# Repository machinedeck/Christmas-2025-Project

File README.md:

# Christmas 2025 Project

## Background

In the Philippines :philippines:, Christmas is usually the most awaited and favorite season of all time. Starting from September, the ambience transitions into a much jollier and brighter side with occassional Mariah Carey's hit _All I Want for Christmas Is You_ playing on the street. This light and invigorating spirit is what sets Filipino culture apart after having been in Europe for two years. Now, being able to return home with all the brand new and more reinforced knowledge I gathered from my master's studies, I encouraged my creativity to embark on a project that utilized the available electronics materials I had at hand. I intentionally finished this project right before Christmas time so I could run  it while we listened to Christmas songs on TV&ndash;which was a really exciting way to celebrate this season!

To start off, this project consisted of two parts: the _**screen**_ and the _**lights**_. Each part has its own microcontroller unit (MCU)&ndash;the **_ATmega328p_**&ndash;mounted on an Arduino UNO board. 

The 8x8 matrix tube **screen** flashes the `MERRY XMAS!` message moving from right to left. On the other hand, the **lights** part consists of four LEDS (red, green, yellow and blue), which have five different lighting configurations with the last one being the combination of the first four in a consecutive manner. More details about them are explained in the later sections.

## Materials
These are the materials I used for each part:

**Screen**
- **1088BS** 8x8 matrix tube screen (Documentation can be found in this [link](https://www.topliteusa.com/uploadfile/2014/0825/A-1088BS.pdf). Similar matrix can be used but _always refer to its datasheet_ because I did not use any driver to run it, and the pins have to be connected accordingly to flash what you intend to show.)
- Eight **1k&ohm;-resistors**
- One **tactile switch**
- **Arduino UNO** development board with **ATmega328p** microncontroller
- Wires
- _Optional:_ One **9V battery**

**Lights**
- Four **LEDs** (can be any color, but I used red, green, yellow and blue)
- Four **1k&ohm;-resistors**
- One **tactile switch**
- **Arduino UNO** development board with **ATmega328p** microncontroller
- Wires
- _Optional:_ One **9V battery**

## Schematic

### Screen

<p align = "center"><b>Figure 1.</b> Schematic diagram of the wire connections of the 1088BS matrix to the Arduino UNO development board controlled by a switch in pull-up setting. I did not find any matrix design in Tinkercad so I just put its detailed schematics as an array of LEDs. This design was created from this website: <a href = "https://www.circuit-diagram.org/editor/">https://www.circuit-diagram.org/editor/</a>.</p>

The general circuit design for the **screen** part is provided above. The matrix represented as an array of LEDs has also been documented as such in its datasheet [here](https://www.topliteusa.com/uploadfile/2014/0825/A-1088BS.pdf). It is important to note that the matrix does not have its own internal resistors as given in **Figure 1**. This is the reason that there are eight 1k&ohm;-resistors included in the materials. There is a switch included which turns the screen _ON_ and _OFF_. However, this is just the circuit connections, and its working function is defined by the Arduino code uploaded to the microcontroller.

### Lights

<p align = "center"><b>Figure 2.</b> Breadboard connections for the four-LED system controlled by a switch in pull-up configuration. Schematics created from <a href = "https://www.tinkercad.com/">https://www.tinkercad.com/</a> using the circuits option.</p>

For this part, there are LED light array configuration as follows, controlled by pressin a button in a chronological order:
- **Case 1:** Lights fade in then fade out
- **Case 2:** Lights blink
- **Case 3:** Light "pulse" going from one LED to the next. Goes to the first LED after it reaches the last LED.
- **Case 4:** Two sets of LEDs alternate blinking
- **Case 5:** Cases 1-4

Once all the cases have been performed, the LEDs just turn off. Pressing the button reinitiates the cases.

## Codes
Before uploading the codes into the microcontrollers, make sure to install the **Arduino IDE**. Set the board to `Arduino UNO` (can be downloaded [here](https://www.arduino.cc/en/software/)) and make sure that there is a port connection. Once initialized, the following codes must be uploaded to two separate Arduino development boards:
- **Screen:** [`screen.ino`](https://github.com/machinedeck/Christmas-2025-Project/blob/main/screen/screen.ino)
- **Lights:** [`lights.ino`](https://github.com/machinedeck/Christmas-2025-Project/blob/main/lights/lights.ino)

For [`screen.ino`](https://github.com/machinedeck/Christmas-2025-Project/blob/main/screen/screen.ino), I had to manually design the array for the `MERRY XMAS!` message in Excel, then convert them into a `.CSV` file to copy the array into Arduino code. All these information can be found in the following files: `screen_data.txt`, `screen_data.csv`, and `screen_data.xlsx`. Moreover, upon researching, it could be impossible to, say, individually control an array element of the matrix at a time. This is where I struggled the most because I initialized the matrix to a some array of 0's and 1's, but I ended up having one column all turned _ON_ when only a few has to be such. For this, **I had to resort to ChatGPT to seek help**. **I am highlighting this point to go back and understand this matter later on**, I just needed to finish it before Christmas.

For [`lights.ino`](https://github.com/machinedeck/Christmas-2025-Project/blob/main/lights/lights.ino), I was mostly inspired by the lighting mechanism of the Christmas lights displayed outside my neighbor's house. That's where I got the idea of changing configurations, but allows the user to change it at will with a switch.

For both codes, I used switches to control their initialization, termination and configurations by utilizing the [`attachInterrupt()`](https://docs.arduino.cc/language-reference/en/functions/external-interrupts/attachInterrupt/). This interrupt function is initialized in the setup.

## Comments
I noticed that for the **lights** part, I noticed some misalignments with the button press and the LED light configuration. I have not quantified this disparity nor possible delay but there could be some synchronization error, or the with the code itself. I noticed this especially in **Case 5**, where it is supposed to start from **Case 1**. However, there were instances where it just turned _OFF_ or does not start with **Case 1**. I suspect that it might have to do with the code because I once ran the script printing a defined "counter" value, and there was a little problem.

Furthermore, I experienced some memory problem during the course of code development. Before this, I was not able to control the lights independently, which I resolved by using the [`millis()`](https://docs.arduino.cc/language-reference/en/functions/time/millis/) function to avoid blocking code with [`delay()`](https://docs.arduino.cc/language-reference/en/functions/time/delay/). Now, with memory, I have realized how efficient programming is important to expedite process and save storage. For this reason I launched this [repository](https://github.com/machinedeck/Firmware-Programming-1) to learn about efficient embedded programming using registers in C++.

## KiCAD
I also tried to make a KiCAD design, which is provided in this [folder](https://github.com/machinedeck/Christmas-2025-Project/tree/main/xmas).

## Disclaimer
I used ChatGPT mainly to debug my codes and/or seek help regarding their functionalities.

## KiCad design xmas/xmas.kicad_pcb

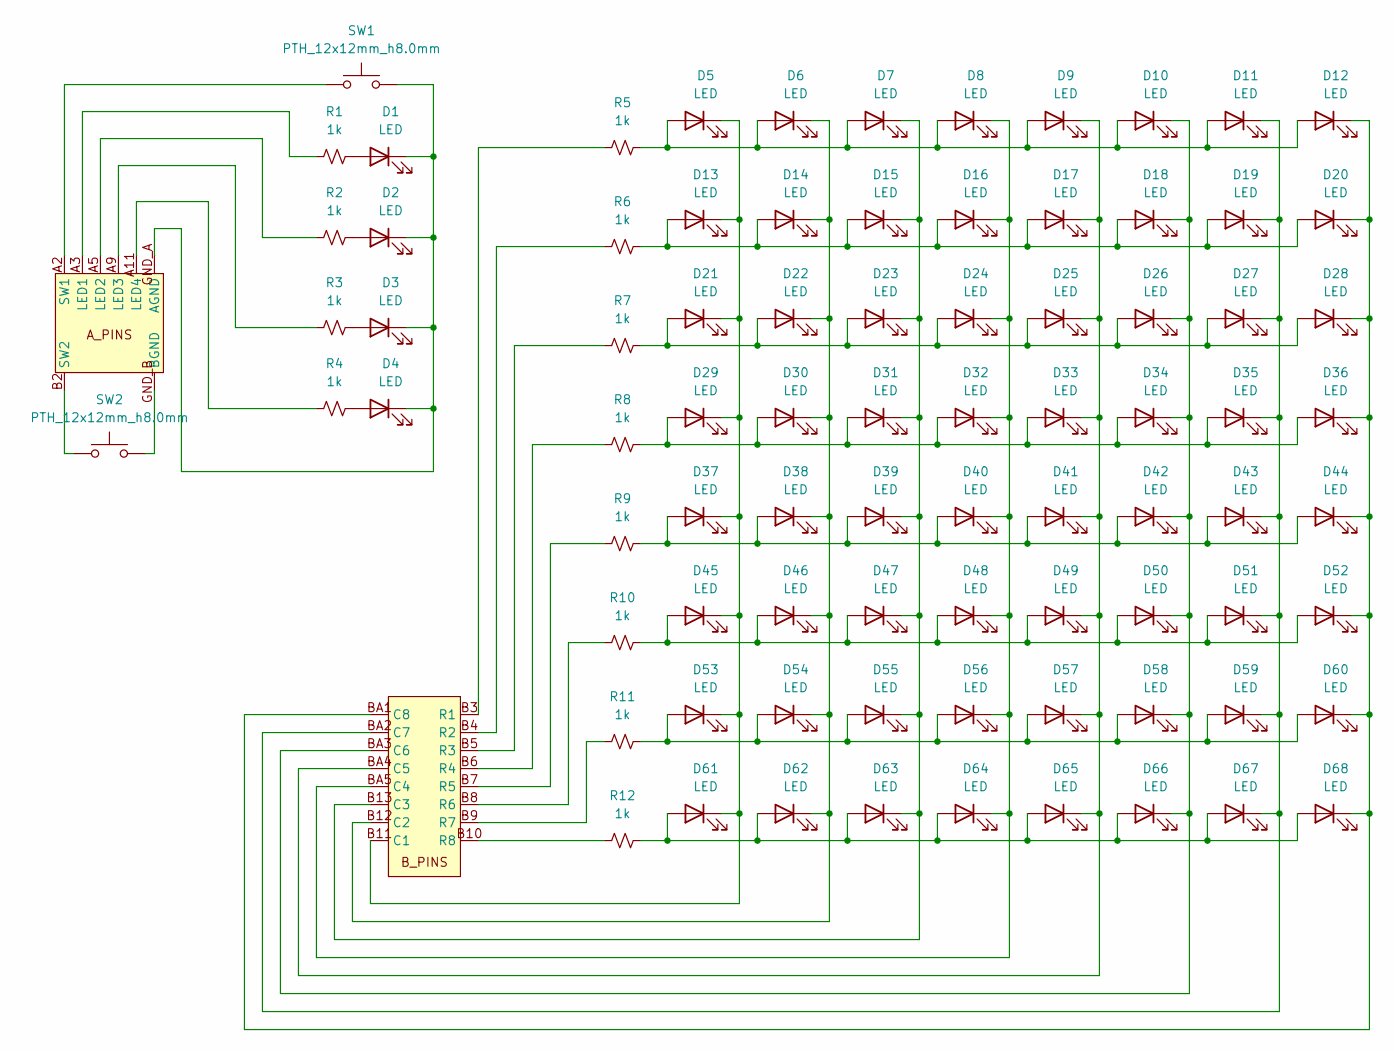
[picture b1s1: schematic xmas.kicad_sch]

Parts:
D1, D2, D3, D4: LED; LED_D3.0mm
D5, D6, D7, D8, D9, D10, D11, D12, D13, D14, D15, D16, D17, D18, D19, D20, D21, D22, D23, D24, D25, D26, D27, D28, D29, D30, D31, D32, D33, D34, D35, D36, D37, D38, D39, D40, D41, D42, D43, D44, D45, D46, D47, D48, D49, D50, D51, D52, D53, D54, D55, D56, D57, D58, D59, D60, D61, D62, D63, D64, D65, D66, D67, D68: LED; LED_D3.0mm_FlatTop
R1, R2, R3, R4, R5, R6, R7, R8, R9, R10, R11, R12: 1k; R_0402_1005Metric
SW1, SW2: PTH_12x12mm_h8.0mm; Push_PTH_12x12mm
U2: a_pins
U4: b_pins

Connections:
unnamed: D1.2 (A), R1.2
unnamed: D1.1 (K), D2.1 (K), D3.1 (K), D4.1 (K), SW1.2, U2.GND_A (AGND)
unnamed: D2.2 (A), R2.2
unnamed: D3.2 (A), R3.2
unnamed: D4.2 (A), R4.2
unnamed: D5.2 (A), D6.2 (A), D7.2 (A), D8.2 (A), D9.2 (A), D10.2 (A), D11.2 (A), D12.2 (A), R5.2
unnamed: D10.1 (K), D18.1 (K), D26.1 (K), D34.1 (K), D42.1 (K), D50.1 (K), D58.1 (K), D66.1 (K), U4.BA3 (C6)
unnamed: D11.1 (K), D19.1 (K), D27.1 (K), D35.1 (K), D43.1 (K), D51.1 (K), D59.1 (K), D67.1 (K), U4.BA2 (C7)
unnamed: D12.1 (K), D20.1 (K), D28.1 (K), D36.1 (K), D44.1 (K), D52.1 (K), D60.1 (K), D68.1 (K), U4.BA1 (C8)
unnamed: D13.2 (A), D14.2 (A), D15.2 (A), D16.2 (A), D17.2 (A), D18.2 (A), D19.2 (A), D20.2 (A), R6.2
unnamed: D5.1 (K), D13.1 (K), D21.1 (K), D29.1 (K), D37.1 (K), D45.1 (K), D53.1 (K), D61.1 (K), U4.B11 (C1)
unnamed: D6.1 (K), D14.1 (K), D22.1 (K), D30.1 (K), D38.1 (K), D46.1 (K), D54.1 (K), D62.1 (K), U4.B12 (C2)
unnamed: D7.1 (K), D15.1 (K), D23.1 (K), D31.1 (K), D39.1 (K), D47.1 (K), D55.1 (K), D63.1 (K), U4.B13 (C3)
unnamed: D8.1 (K), D16.1 (K), D24.1 (K), D32.1 (K), D40.1 (K), D48.1 (K), D56.1 (K), D64.1 (K), U4.BA5 (C4)
unnamed: D9.1 (K), D17.1 (K), D25.1 (K), D33.1 (K), D41.1 (K), D49.1 (K), D57.1 (K), D65.1 (K), U4.BA4 (C5)
unnamed: D21.2 (A), D22.2 (A), D23.2 (A), D24.2 (A), D25.2 (A), D26.2 (A), D27.2 (A), D28.2 (A), R7.2
unnamed: D29.2 (A), D30.2 (A), D31.2 (A), D32.2 (A), D33.2 (A), D34.2 (A), D35.2 (A), D36.2 (A), R8.2
unnamed: D37.2 (A), D38.2 (A), D39.2 (A), D40.2 (A), D41.2 (A), D42.2 (A), D43.2 (A), D44.2 (A), R9.2
unnamed: D45.2 (A), D46.2 (A), D47.2 (A), D48.2 (A), D49.2 (A), D50.2 (A), D51.2 (A), D52.2 (A), R10.2
unnamed: D53.2 (A), D54.2 (A), D55.2 (A), D56.2 (A), D57.2 (A), D58.2 (A), D59.2 (A), D60.2 (A), R11.2
unnamed: D61.2 (A), D62.2 (A), D63.2 (A), D64.2 (A), D65.2 (A), D66.2 (A), D67.2 (A), D68.2 (A), R12.2
unnamed: SW2.2, U2.GND_B (BGND)
unnamed: R1.1, U2.A3 (LED1)
unnamed: R2.1, U2.A5 (LED2)
unnamed: R3.1, U2.A9 (LED3)
unnamed: R4.1, U2.A11 (LED4)
unnamed: SW1.1, U2.A2 (SW1)
unnamed: SW2.1, U2.B2 (SW2)
unnamed: R5.1, U4.B3 (R1)
unnamed: R6.1, U4.B4 (R2)
unnamed: R7.1, U4.B5 (R3)
unnamed: R8.1, U4.B6 (R4)
unnamed: R9.1, U4.B7 (R5)
unnamed: R10.1, U4.B8 (R6)
unnamed: R11.1, U4.B9 (R7)
unnamed: R12.1, U4.B10 (R8)

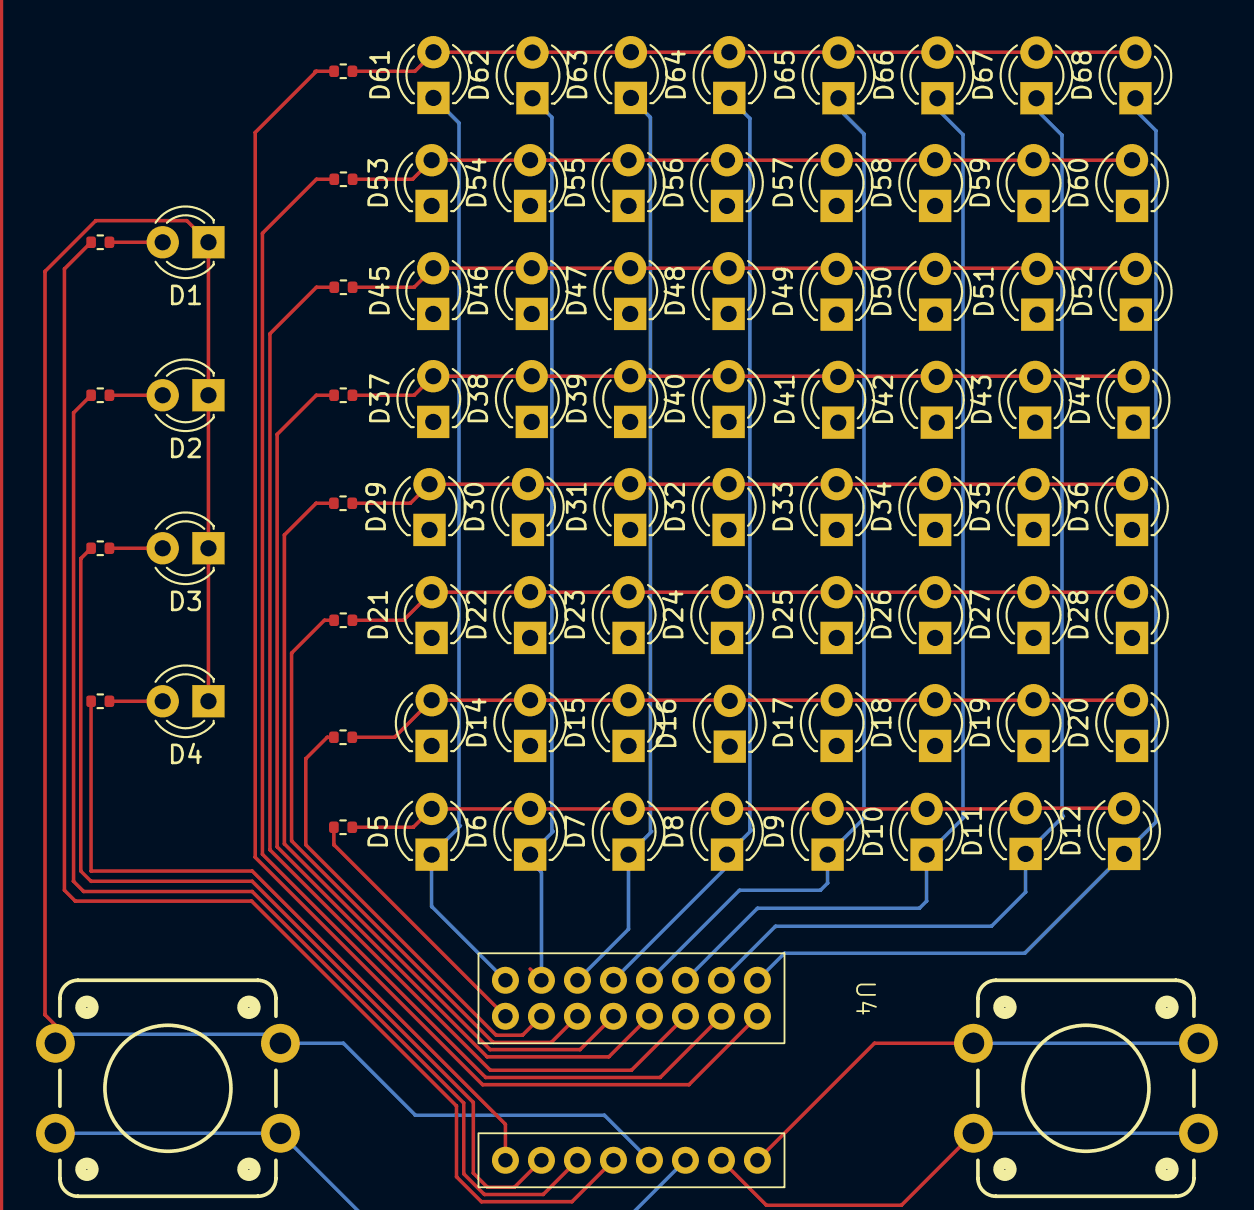
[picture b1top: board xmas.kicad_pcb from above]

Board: 2 copper layers, 84 parts (0 on the bottom side), 36 nets.

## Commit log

2025-12-27 Christmas project files
2025-12-27 images
2025-12-27 prototype
2025-12-27 Rename IMG20251227223522.jpg to main.jpg
